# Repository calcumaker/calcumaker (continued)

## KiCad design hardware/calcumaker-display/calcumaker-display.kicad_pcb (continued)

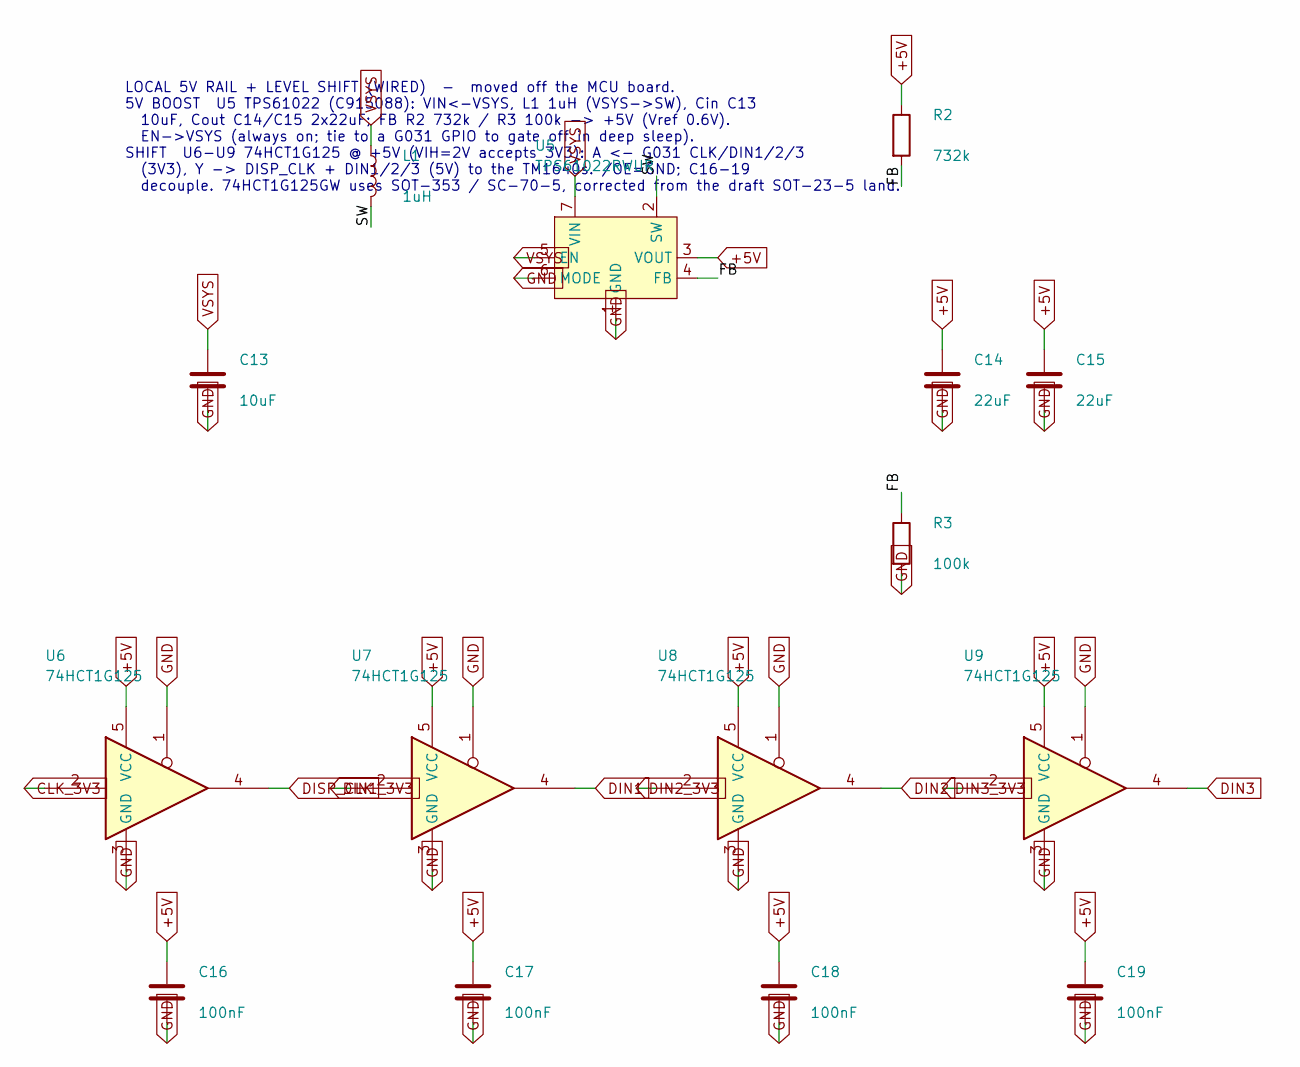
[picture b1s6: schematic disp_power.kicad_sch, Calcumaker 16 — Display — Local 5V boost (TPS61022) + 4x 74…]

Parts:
C13: 10uF; C_0603_1608Metric; LCSC C15850
C14, C15: 22uF; C_0603_1608Metric; LCSC C45783
C16, C17, C18, C19: 100nF; C_0402_1005Metric; LCSC C1525
L1: 1uH; L_0805_2012Metric; MPN FTC201610S1R0MBCA; LCSC C5832342
R2: 732k; R_0402_1005Metric
R3: 100k; R_0402_1005Metric; LCSC C25741
U5: TPS61022RWUR; Texas_RWU0007A_VQFN-7_2x2mm_P0.5mm; MPN TPS61022RWUR; LCSC C915088
U6, U7, U8, U9: 74HCT1G125; SOT-353_SC-70-5; MPN 74HCT1G125GW; LCSC C547448

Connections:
+5V: C14.1, C15.1, C16.1, C17.1, C18.1, C19.1, R2.1, U5.3 (VOUT), U6.5 (VCC), U7.5 (VCC), U8.5 (VCC), U9.5 (VCC); also elsewhere on the board
/DispPower/FB: R2.2, R3.1, U5.4 (FB)
/DispPower/SW: L1.2, U5.2 (SW)
CLK_3V3: U6.2; also elsewhere on the board
DIN1: U7.4; also elsewhere on the board
DIN1_3V3: U7.2; also elsewhere on the board
DIN2: U8.4; also elsewhere on the board
DIN2_3V3: U8.2; also elsewhere on the board
DIN3: U9.4; also elsewhere on the board
DIN3_3V3: U9.2; also elsewhere on the board
DISP_CLK: U6.4; also elsewhere on the board
GND: C13.2, C14.2, C15.2, C16.2, C17.2, C18.2, C19.2, R3.2, U5.1 (GND), U5.6 (MODE), U6.1, U6.3 (GND), U7.1, U7.3 (GND), U8.1, U8.3 (GND), U9.1, U9.3 (GND); also elsewhere on the board
VSYS: C13.1, L1.1, U5.5 (EN), U5.7 (VIN); also elsewhere on the board

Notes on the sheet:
LOCAL 5V RAIL + LEVEL SHIFT (WIRED) - moved off the MCU board. 5V BOOST U5 TPS61022 (C915088): VIN<-VSYS, L1 1uH (VSYS->SW), Cin C13 10uF, Cout C14/C15 2x22uF; FB R2 732k / R3 100k -> +5V (Vref 0.6V). EN->VSYS (always on; tie to a G031 GPIO to gate off in deep sleep). SHIFT U6-U9 74HCT1G125 @ +5V (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

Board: 2 copper layers, 86 parts (37 on the bottom side), 96 nets, no tracks yet.

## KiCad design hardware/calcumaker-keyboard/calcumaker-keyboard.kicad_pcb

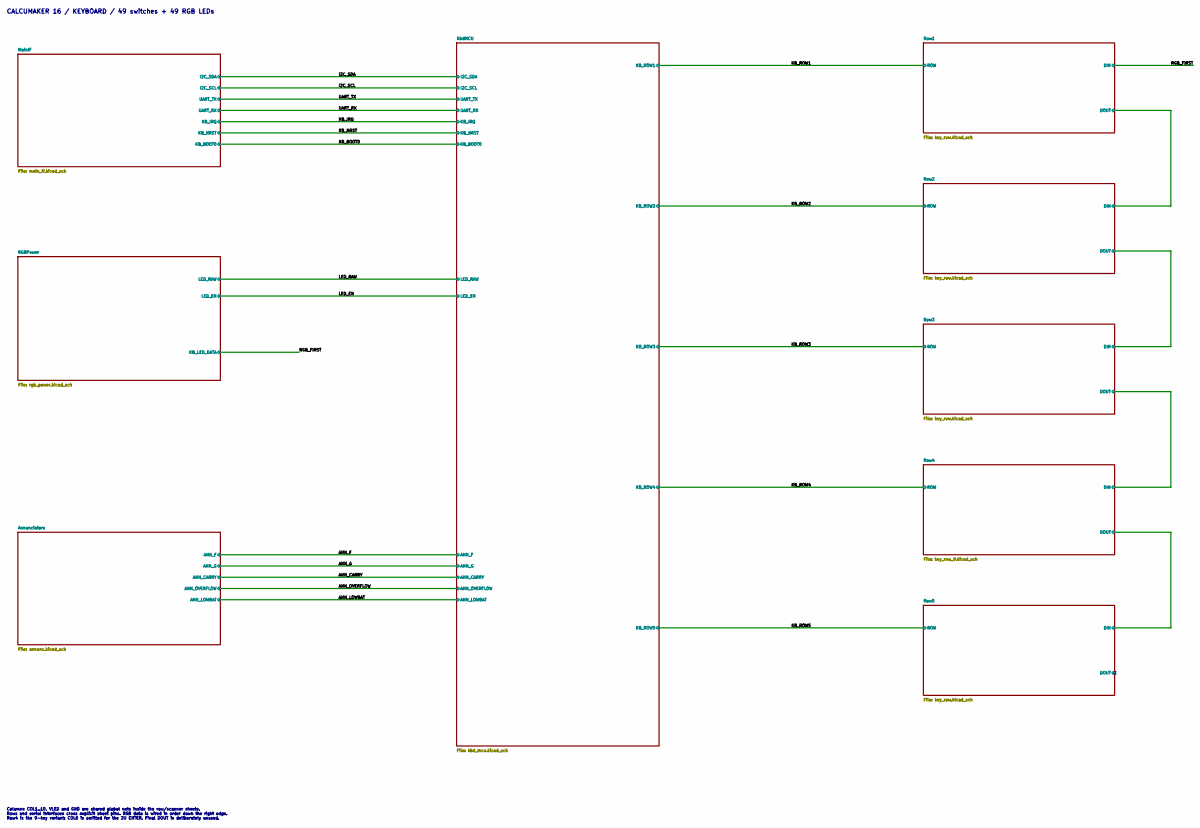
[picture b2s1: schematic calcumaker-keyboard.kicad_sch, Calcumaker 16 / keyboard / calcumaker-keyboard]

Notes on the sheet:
Columns COL1..10, VLED and GND are shared global nets inside the row/scanner sheets. Rows and serial interfaces cross explicit sheet pins. RGB data is wired in order down the right edge. Row4 is the 9-key variant: COL6 is omitted for the 2U ENTER. Final DOUT is deliberately unused.
CALCUMAKER 16 / KEYBOARD / 49 switches + 49 RGB LEDs

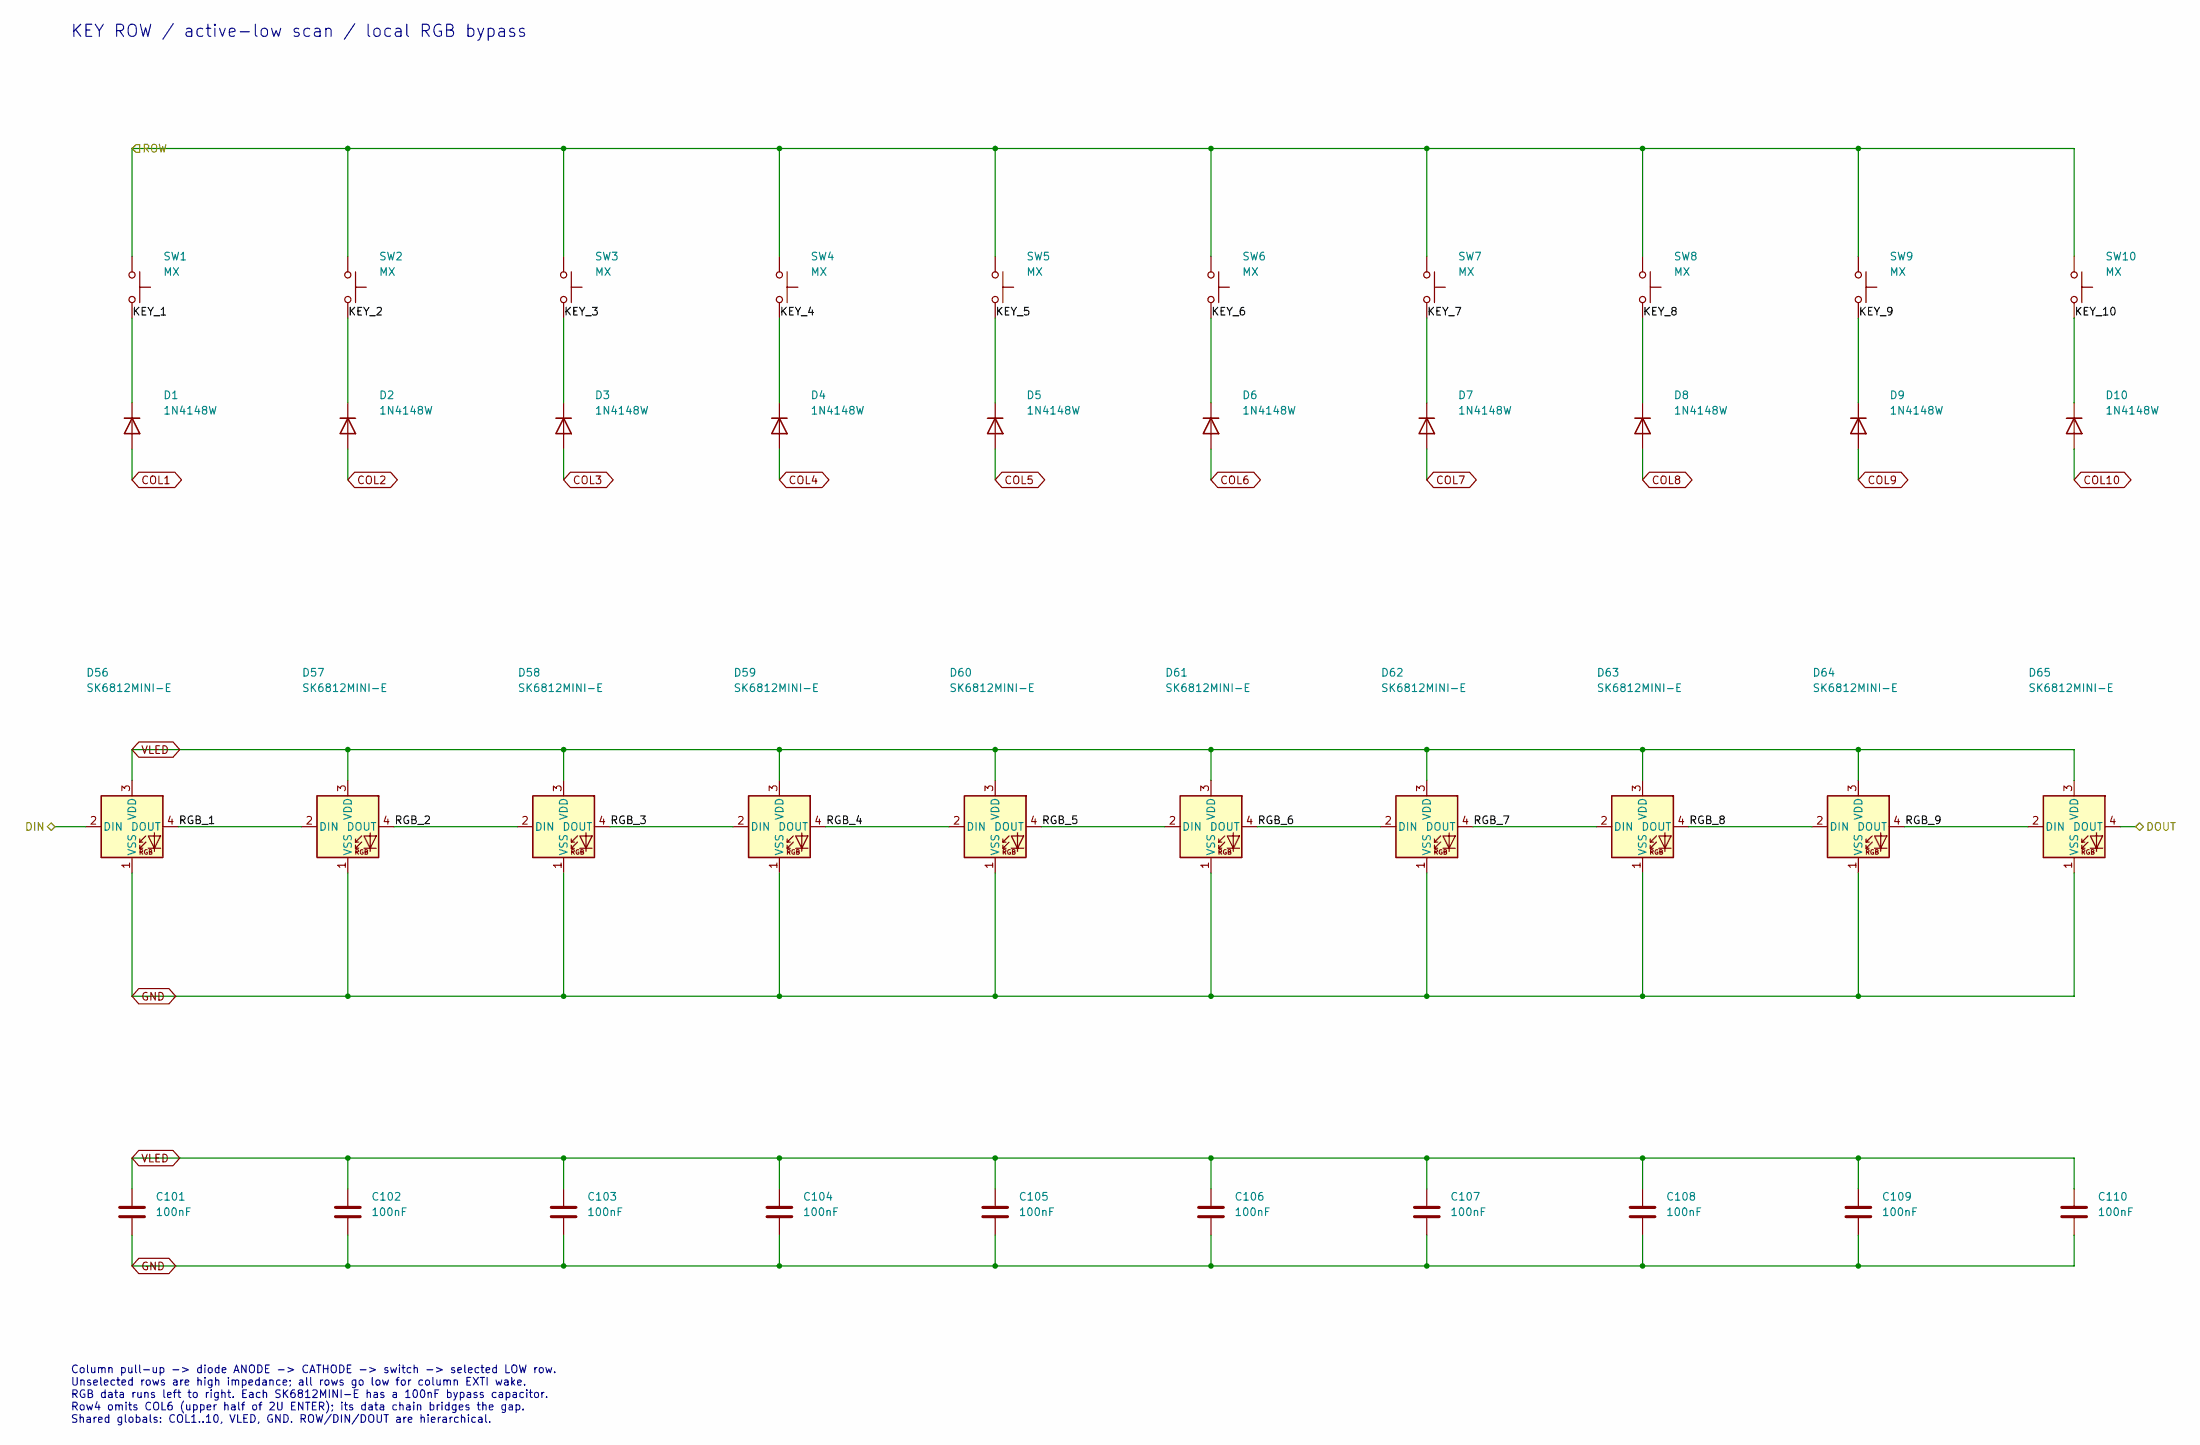
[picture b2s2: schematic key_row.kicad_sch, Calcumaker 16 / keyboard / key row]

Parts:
C101, C102, C103, C104, C105, C106, C107, C108, C109, C110: 100nF; C_0402_1005Metric
D1, D2, D3, D4, D5, D6, D7, D8, D9, D10: 1N4148W; D_SOD-123; MPN 1N4148W; LCSC C81598
D56, D57, D58, D59, D60, D61, D62, D63, D64, D65: SK6812MINI-E; LED_SK6812MINI-E_3.2x2.8mm_P1.5mm_ReverseMount; MPN SK6812MINI-E; LCSC C5149201
SW1, SW2, SW3, SW4, SW5, SW6, SW7, SW8, SW9, SW10: MX; SW_MX_HS_CPG151101S11_1u

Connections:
/KB_ROW1: SW1.1, SW2.1, SW3.1, SW4.1, SW5.1, SW6.1, SW7.1, SW8.1, SW9.1, SW10.1; also elsewhere on the board
/RGB_FIRST: D56.2 (DIN); also elsewhere on the board
/Row1/DOUT: D65.4 (DOUT); also elsewhere on the board
/Row1/KEY_1: D1.1 (K), SW1.2
/Row1/KEY_2: D2.1 (K), SW2.2
/Row1/KEY_3: D3.1 (K), SW3.2
/Row1/KEY_4: D4.1 (K), SW4.2
/Row1/KEY_5: D5.1 (K), SW5.2
/Row1/KEY_6: D6.1 (K), SW6.2
/Row1/KEY_7: D7.1 (K), SW7.2
/Row1/KEY_8: D8.1 (K), SW8.2
/Row1/KEY_9: D9.1 (K), SW9.2
/Row1/KEY_10: D10.1 (K), SW10.2
/Row1/RGB_1: D56.4 (DOUT), D57.2 (DIN)
/Row1/RGB_2: D57.4 (DOUT), D58.2 (DIN)
/Row1/RGB_3: D58.4 (DOUT), D59.2 (DIN)
/Row1/RGB_4: D59.4 (DOUT), D60.2 (DIN)
/Row1/RGB_5: D60.4 (DOUT), D61.2 (DIN)
/Row1/RGB_6: D61.4 (DOUT), D62.2 (DIN)
/Row1/RGB_7: D62.4 (DOUT), D63.2 (DIN)
/Row1/RGB_8: D63.4 (DOUT), D64.2 (DIN)
/Row1/RGB_9: D64.4 (DOUT), D65.2 (DIN)
COL1: D1.2 (A); also elsewhere on the board
COL2: D2.2 (A); also elsewhere on the board
COL3: D3.2 (A); also elsewhere on the board
COL4: D4.2 (A); also elsewhere on the board
COL5: D5.2 (A); also elsewhere on the board
COL6: D6.2 (A); also elsewhere on the board
COL7: D7.2 (A); also elsewhere on the board
COL8: D8.2 (A); also elsewhere on the board
COL9: D9.2 (A); also elsewhere on the board
COL10: D10.2 (A); also elsewhere on the board
GND: C101.2, C102.2, C103.2, C104.2, C105.2, C106.2, C107.2, C108.2, C109.2, C110.2, D56.1 (VSS), D57.1 (VSS), D58.1 (VSS), D59.1 (VSS), D60.1 (VSS), D61.1 (VSS), D62.1 (VSS), D63.1 (VSS), D64.1 (VSS), D65.1 (VSS); also elsewhere on the board
VLED: C101.1, C102.1, C103.1, C104.1, C105.1, C106.1, C107.1, C108.1, C109.1, C110.1, D56.3 (VDD), D57.3 (VDD), D58.3 (VDD), D59.3 (VDD), D60.3 (VDD), D61.3 (VDD), D62.3 (VDD), D63.3 (VDD), D64.3 (VDD), D65.3 (VDD); also elsewhere on the board

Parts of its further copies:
C111, C112, C113, C114, C115, C116, C117, C118, C119, C120, C121, C122, C123, C124, C125, C126, C127, C128, C129, C130, C141, C142, C143, C144, C145, C146, C147, C148, C149, C150: 100nF; C_0402_1005Metric
D11, D12, D13, D14, D15, D16, D17, D18, D19, D20, D21, D22, D23, D24, D25, D26, D27, D28, D29, D30, D41, D42, D43, D44, D45, D46, D47, D48, D49, D50: 1N4148W; D_SOD-123; MPN 1N4148W; LCSC C81598
D66, D67, D68, D69, D70, D71, D72, D73, D74, D75, D76, D77, D78, D79, D80, D81, D82, D83, D84, D85, D96, D97, D98, D99, D100, D101, D102, D103, D104, D105: SK6812MINI-E; LED_SK6812MINI-E_3.2x2.8mm_P1.5mm_ReverseMount; MPN SK6812MINI-E; LCSC C5149201
SW11, SW12, SW13, SW14, SW15, SW16, SW17, SW18, SW19, SW20, SW21, SW22, SW23, SW24, SW25, SW26, SW27, SW28, SW29, SW30, SW41, SW42, SW43, SW44, SW45, SW46, SW47, SW48, SW49, SW50: MX; SW_MX_HS_CPG151101S11_1u

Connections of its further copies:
/KB_ROW2: SW11.1, SW12.1, SW13.1, SW14.1, SW15.1, SW16.1, SW17.1, SW18.1, SW19.1, SW20.1; also elsewhere on the board
/KB_ROW3: SW21.1, SW22.1, SW23.1, SW24.1, SW25.1, SW26.1, SW27.1, SW28.1, SW29.1, SW30.1; also elsewhere on the board
/KB_ROW5: SW41.1, SW42.1, SW43.1, SW44.1, SW45.1, SW46.1, SW47.1, SW48.1, SW49.1, SW50.1; also elsewhere on the board
/Row1/DOUT: D66.2 (DIN); also elsewhere on the board
/Row2/DOUT: D75.4 (DOUT), D76.2 (DIN)
/Row2/KEY_1: D11.1 (K), SW11.2
/Row2/KEY_2: D12.1 (K), SW12.2
/Row2/KEY_3: D13.1 (K), SW13.2
/Row2/KEY_4: D14.1 (K), SW14.2
/Row2/KEY_5: D15.1 (K), SW15.2
/Row2/KEY_6: D16.1 (K), SW16.2
/Row2/KEY_7: D17.1 (K), SW17.2
/Row2/KEY_8: D18.1 (K), SW18.2
/Row2/KEY_9: D19.1 (K), SW19.2
/Row2/KEY_10: D20.1 (K), SW20.2
/Row2/RGB_1: D66.4 (DOUT), D67.2 (DIN)
/Row2/RGB_2: D67.4 (DOUT), D68.2 (DIN)
/Row2/RGB_3: D68.4 (DOUT), D69.2 (DIN)
/Row2/RGB_4: D69.4 (DOUT), D70.2 (DIN)
/Row2/RGB_5: D70.4 (DOUT), D71.2 (DIN)
/Row2/RGB_6: D71.4 (DOUT), D72.2 (DIN)
/Row2/RGB_7: D72.4 (DOUT), D73.2 (DIN)
/Row2/RGB_8: D73.4 (DOUT), D74.2 (DIN)
/Row2/RGB_9: D74.4 (DOUT), D75.2 (DIN)
/Row3/DOUT: D85.4 (DOUT); also elsewhere on the board
/Row3/KEY_1: D21.1 (K), SW21.2
/Row3/KEY_2: D22.1 (K), SW22.2
/Row3/KEY_3: D23.1 (K), SW23.2
/Row3/KEY_4: D24.1 (K), SW24.2
/Row3/KEY_5: D25.1 (K), SW25.2
/Row3/KEY_6: D26.1 (K), SW26.2
/Row3/KEY_7: D27.1 (K), SW27.2
/Row3/KEY_8: D28.1 (K), SW28.2
/Row3/KEY_9: D29.1 (K), SW29.2
/Row3/KEY_10: D30.1 (K), SW30.2
/Row3/RGB_1: D76.4 (DOUT), D77.2 (DIN)
/Row3/RGB_2: D77.4 (DOUT), D78.2 (DIN)
/Row3/RGB_3: D78.4 (DOUT), D79.2 (DIN)
/Row3/RGB_4: D79.4 (DOUT), D80.2 (DIN)
/Row3/RGB_5: D80.4 (DOUT), D81.2 (DIN)
/Row3/RGB_6: D81.4 (DOUT), D82.2 (DIN)
/Row3/RGB_7: D82.4 (DOUT), D83.2 (DIN)
/Row3/RGB_8: D83.4 (DOUT), D84.2 (DIN)
/Row3/RGB_9: D84.4 (DOUT), D85.2 (DIN)
/Row4/DOUT: D96.2 (DIN); also elsewhere on the board
/Row5/DOUT: D105.4 (DOUT)
/Row5/KEY_1: D41.1 (K), SW41.2
/Row5/KEY_2: D42.1 (K), SW42.2
/Row5/KEY_3: D43.1 (K), SW43.2
/Row5/KEY_4: D44.1 (K), SW44.2
/Row5/KEY_5: D45.1 (K), SW45.2
/Row5/KEY_6: D46.1 (K), SW46.2
/Row5/KEY_7: D47.1 (K), SW47.2
/Row5/KEY_8: D48.1 (K), SW48.2
/Row5/KEY_9: D49.1 (K), SW49.2
/Row5/KEY_10: D50.1 (K), SW50.2
/Row5/RGB_1: D96.4 (DOUT), D97.2 (DIN)
/Row5/RGB_2: D97.4 (DOUT), D98.2 (DIN)
/Row5/RGB_3: D98.4 (DOUT), D99.2 (DIN)
/Row5/RGB_4: D99.4 (DOUT), D100.2 (DIN)
/Row5/RGB_5: D100.4 (DOUT), D101.2 (DIN)
/Row5/RGB_6: D101.4 (DOUT), D102.2 (DIN)
/Row5/RGB_7: D102.4 (DOUT), D103.2 (DIN)
/Row5/RGB_8: D103.4 (DOUT), D104.2 (DIN)
/Row5/RGB_9: D104.4 (DOUT), D105.2 (DIN)
COL1: D11.2 (A), D21.2 (A), D41.2 (A); also elsewhere on the board
COL2: D12.2 (A), D22.2 (A), D42.2 (A); also elsewhere on the board
COL3: D13.2 (A), D23.2 (A), D43.2 (A); also elsewhere on the board
COL4: D14.2 (A), D24.2 (A), D44.2 (A); also elsewhere on the board
COL5: D15.2 (A), D25.2 (A), D45.2 (A); also elsewhere on the board
COL6: D16.2 (A), D26.2 (A), D46.2 (A); also elsewhere on the board
COL7: D17.2 (A), D27.2 (A), D47.2 (A); also elsewhere on the board
COL8: D18.2 (A), D28.2 (A), D48.2 (A); also elsewhere on the board
COL9: D19.2 (A), D29.2 (A), D49.2 (A); also elsewhere on the board
COL10: D20.2 (A), D30.2 (A), D50.2 (A); also elsewhere on the board
GND: C111.2, C112.2, C113.2, C114.2, C115.2, C116.2, C117.2, C118.2, C119.2, C120.2, C121.2, C122.2, C123.2, C124.2, C125.2, C126.2, C127.2, C128.2, C129.2, C130.2, C141.2, C142.2, C143.2, C144.2, C145.2, C146.2, C147.2, C148.2, C149.2, C150.2, D66.1 (VSS), D67.1 (VSS), D68.1 (VSS), D69.1 (VSS), D70.1 (VSS), D71.1 (VSS), D72.1 (VSS), D73.1 (VSS), D74.1 (VSS), D75.1 (VSS), D76.1 (VSS), D77.1 (VSS), D78.1 (VSS), D79.1 (VSS), D80.1 (VSS), D81.1 (VSS), D82.1 (VSS), D83.1 (VSS), D84.1 (VSS), D85.1 (VSS), D96.1 (VSS), D97.1 (VSS), D98.1 (VSS), D99.1 (VSS), D100.1 (VSS), D101.1 (VSS), D102.1 (VSS), D103.1 (VSS), D104.1 (VSS), D105.1 (VSS); also elsewhere on the board
VLED: C111.1, C112.1, C113.1, C114.1, C115.1, C116.1, C117.1, C118.1, C119.1, C120.1, C121.1, C122.1, C123.1, C124.1, C125.1, C126.1, C127.1, C128.1, C129.1, C130.1, C141.1, C142.1, C143.1, C144.1, C145.1, C146.1, C147.1, C148.1, C149.1, C150.1, D66.3 (VDD), D67.3 (VDD), D68.3 (VDD), D69.3 (VDD), D70.3 (VDD), D71.3 (VDD), D72.3 (VDD), D73.3 (VDD), D74.3 (VDD), D75.3 (VDD), D76.3 (VDD), D77.3 (VDD), D78.3 (VDD), D79.3 (VDD), D80.3 (VDD), D81.3 (VDD), D82.3 (VDD), D83.3 (VDD), D84.3 (VDD), D85.3 (VDD), D96.3 (VDD), D97.3 (VDD), D98.3 (VDD), D99.3 (VDD), D100.3 (VDD), D101.3 (VDD), D102.3 (VDD), D103.3 (VDD), D104.3 (VDD), D105.3 (VDD); also elsewhere on the board

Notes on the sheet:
KEY ROW / active-low scan / local RGB bypass
Column pull-up -> diode ANODE -> CATHODE -> switch -> selected LOW row. Unselected rows are high impedance; all rows go low for column EXTI wake. RGB data runs left to right. Each SK6812MINI-E has a 100nF bypass capacitor. Row4 omits COL6 (upper half of 2U ENTER); its data chain bridges the gap. Sh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

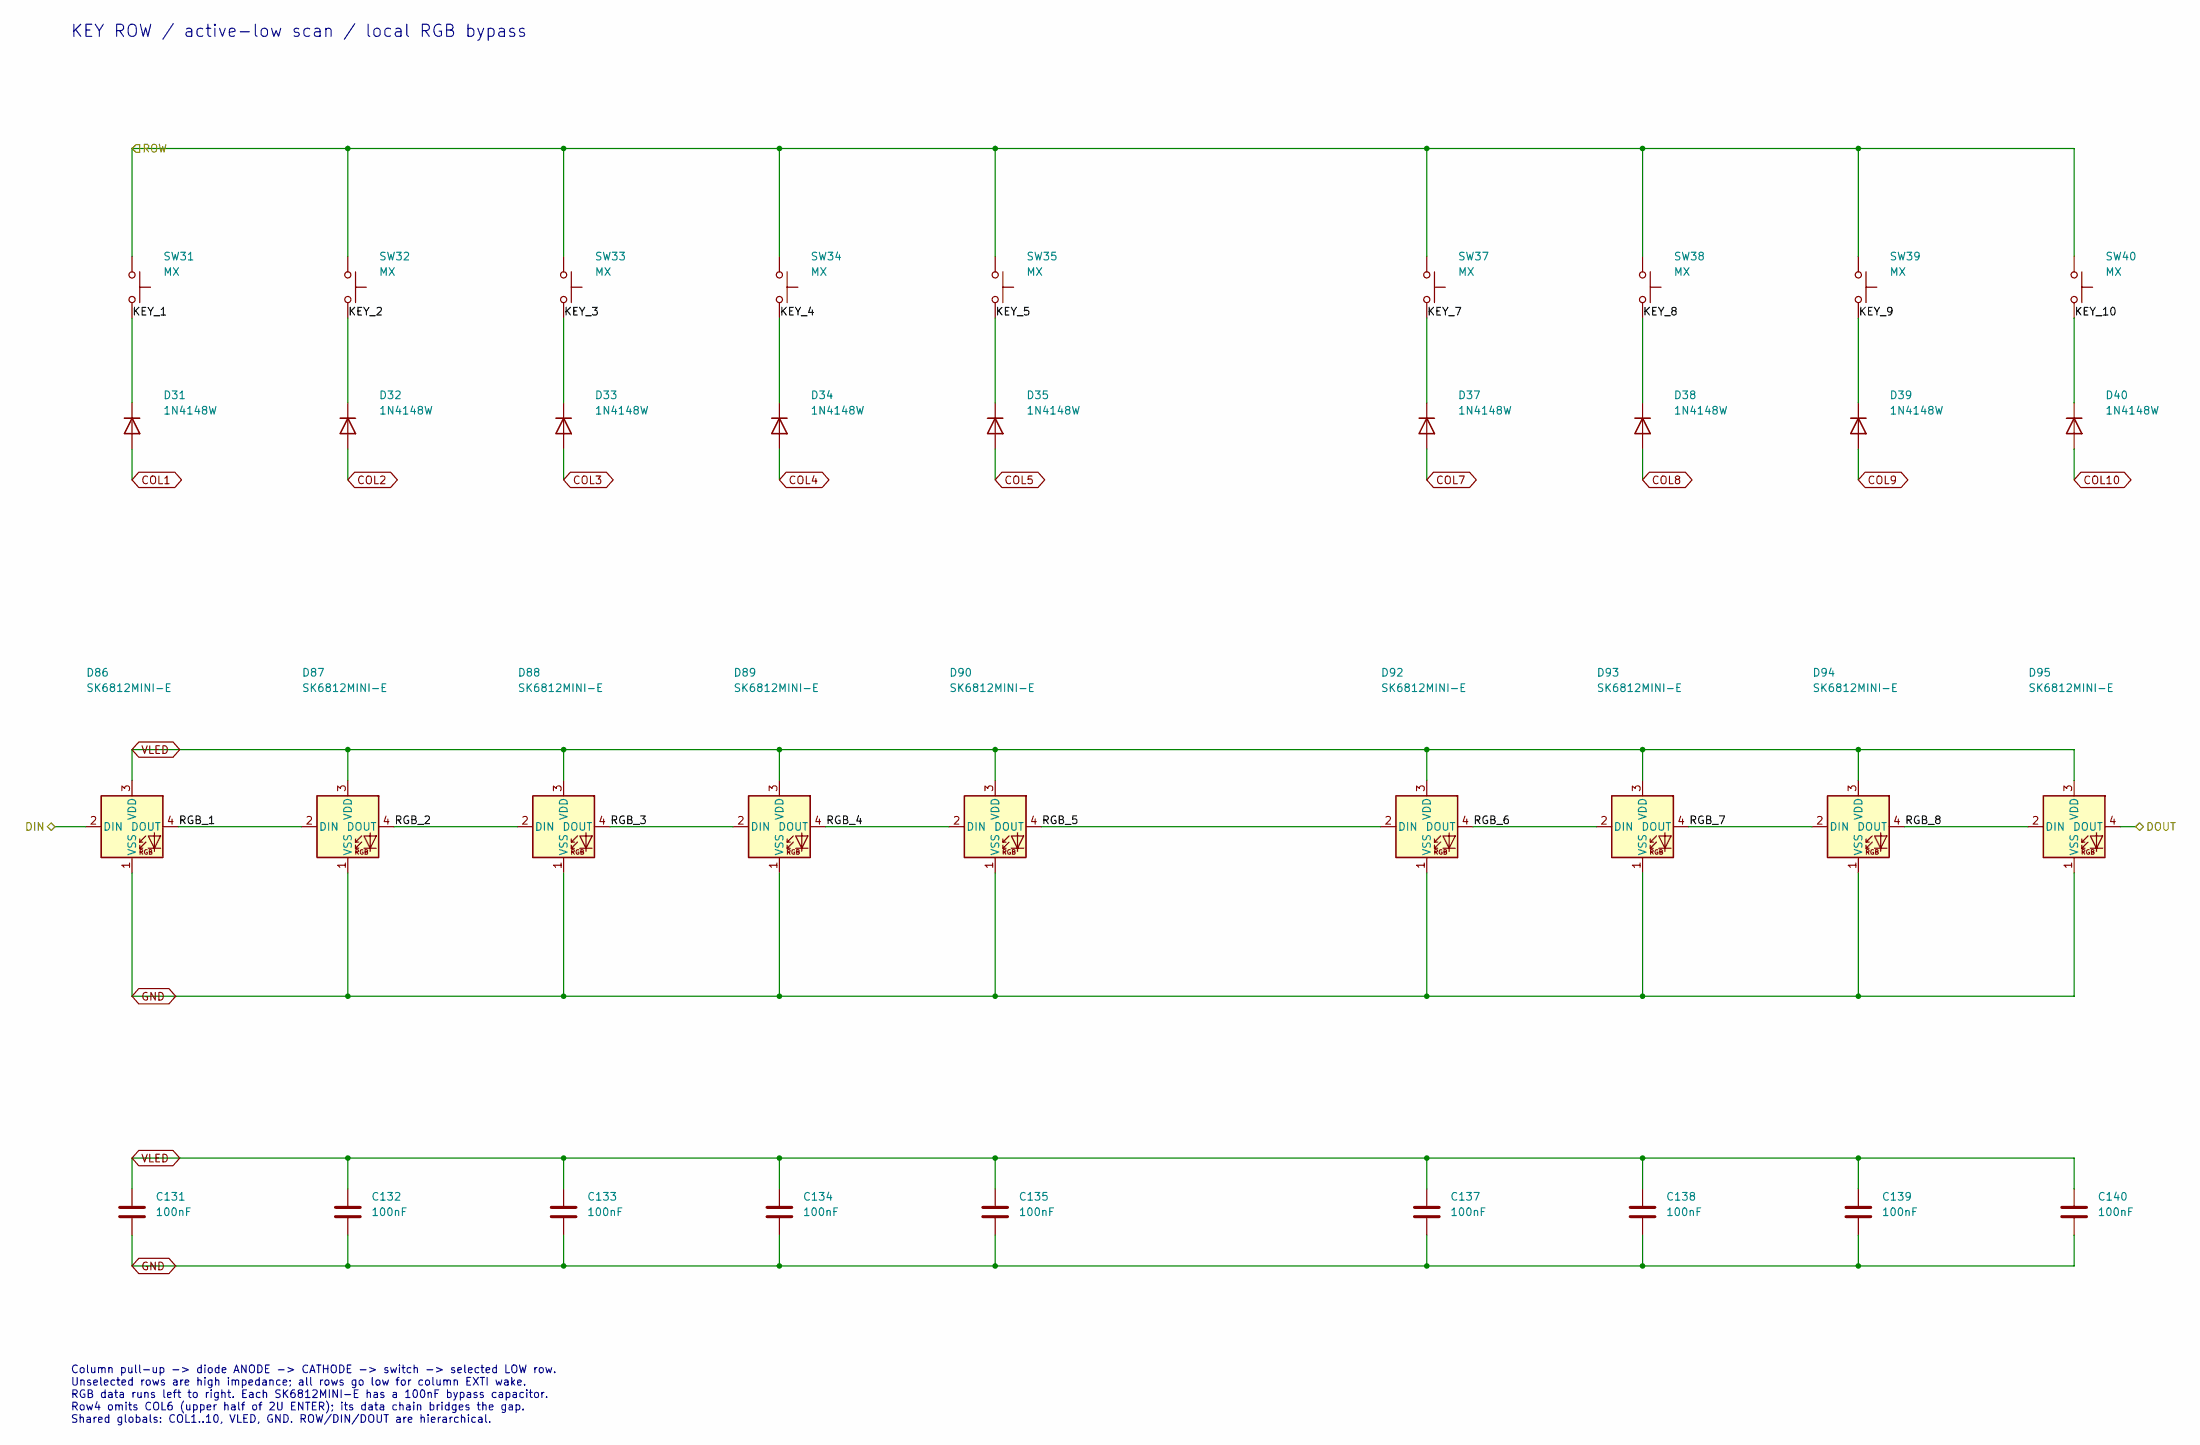
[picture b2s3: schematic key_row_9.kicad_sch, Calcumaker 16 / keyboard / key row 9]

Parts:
C131, C132, C133, C134, C135, C137, C138, C139, C140: 100nF; C_0402_1005Metric
D31, D32, D33, D34, D35, D37, D38, D39, D40: 1N4148W; D_SOD-123; MPN 1N4148W; LCSC C81598
D86, D87, D88, D89, D90, D92, D93, D94, D95: SK6812MINI-E; LED_SK6812MINI-E_3.2x2.8mm_P1.5mm_ReverseMount; MPN SK6812MINI-E; LCSC C5149201
SW31, SW32, SW33, SW34, SW35, SW37, SW38, SW39, SW40: MX; SW_MX_HS_CPG151101S11_1u

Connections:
/KB_ROW4: SW31.1, SW32.1, SW33.1, SW34.1, SW35.1, SW37.1, SW38.1, SW39.1, SW40.1; also elsewhere on the board
/Row3/DOUT: D86.2 (DIN); also elsewhere on the board
/Row4/DOUT: D95.4 (DOUT); also elsewhere on the board
/Row4/KEY_1: D31.1 (K), SW31.2
/Row4/KEY_2: D32.1 (K), SW32.2
/Row4/KEY_3: D33.1 (K), SW33.2
/Row4/KEY_4: D34.1 (K), SW34.2
/Row4/KEY_5: D35.1 (K), SW35.2
/Row4/KEY_7: D37.1 (K), SW37.2
/Row4/KEY_8: D38.1 (K), SW38.2
/Row4/KEY_9: D39.1 (K), SW39.2
/Row4/KEY_10: D40.1 (K), SW40.2
/Row4/RGB_1: D86.4 (DOUT), D87.2 (DIN)
/Row4/RGB_2: D87.4 (DOUT), D88.2 (DIN)
/Row4/RGB_3: D88.4 (DOUT), D89.2 (DIN)
/Row4/RGB_4: D89.4 (DOUT), D90.2 (DIN)
/Row4/RGB_5: D90.4 (DOUT), D92.2 (DIN)
/Row4/RGB_6: D92.4 (DOUT), D93.2 (DIN)
/Row4/RGB_7: D93.4 (DOUT), D94.2 (DIN)
/Row4/RGB_8: D94.4 (DOUT), D95.2 (DIN)
COL1: D31.2 (A); also elsewhere on the board
COL2: D32.2 (A); also elsewhere on the board
COL3: D33.2 (A); also elsewhere on the board
COL4: D34.2 (A); also elsewhere on the board
COL5: D35.2 (A); also elsewhere on the board
COL7: D37.2 (A); also elsewhere on the board
COL8: D38.2 (A); also elsewhere on the board
COL9: D39.2 (A); also elsewhere on the board
COL10: D40.2 (A); also elsewhere on the board
GND: C131.2, C132.2, C133.2, C134.2, C135.2, C137.2, C138.2, C139.2, C140.2, D86.1 (VSS), D87.1 (VSS), D88.1 (VSS), D89.1 (VSS), D90.1 (VSS), D92.1 (VSS), D93.1 (VSS), D94.1 (VSS), D95.1 (VSS); also elsewhere on the board
VLED: C131.1, C132.1, C133.1, C134.1, C135.1, C137.1, C138.1, C139.1, C140.1, D86.3 (VDD), D87.3 (VDD), D88.3 (VDD), D89.3 (VDD), D90.3 (VDD), D92.3 (VDD), D93.3 (VDD), D94.3 (VDD), D95.3 (VDD); also elsewhere on the board

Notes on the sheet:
Column pull-up -> diode ANODE -> CATHODE -> switch -> selected LOW row. Unselected rows are high impedance; all rows go low for column EXTI wake. RGB data runs left to right. Each SK6812MINI-E has a 100nF bypass capacitor. Row4 omits COL6 (upper half of 2U ENTER); its data chain bridges the gap. Sh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
KEY ROW / active-low scan / local RGB bypass

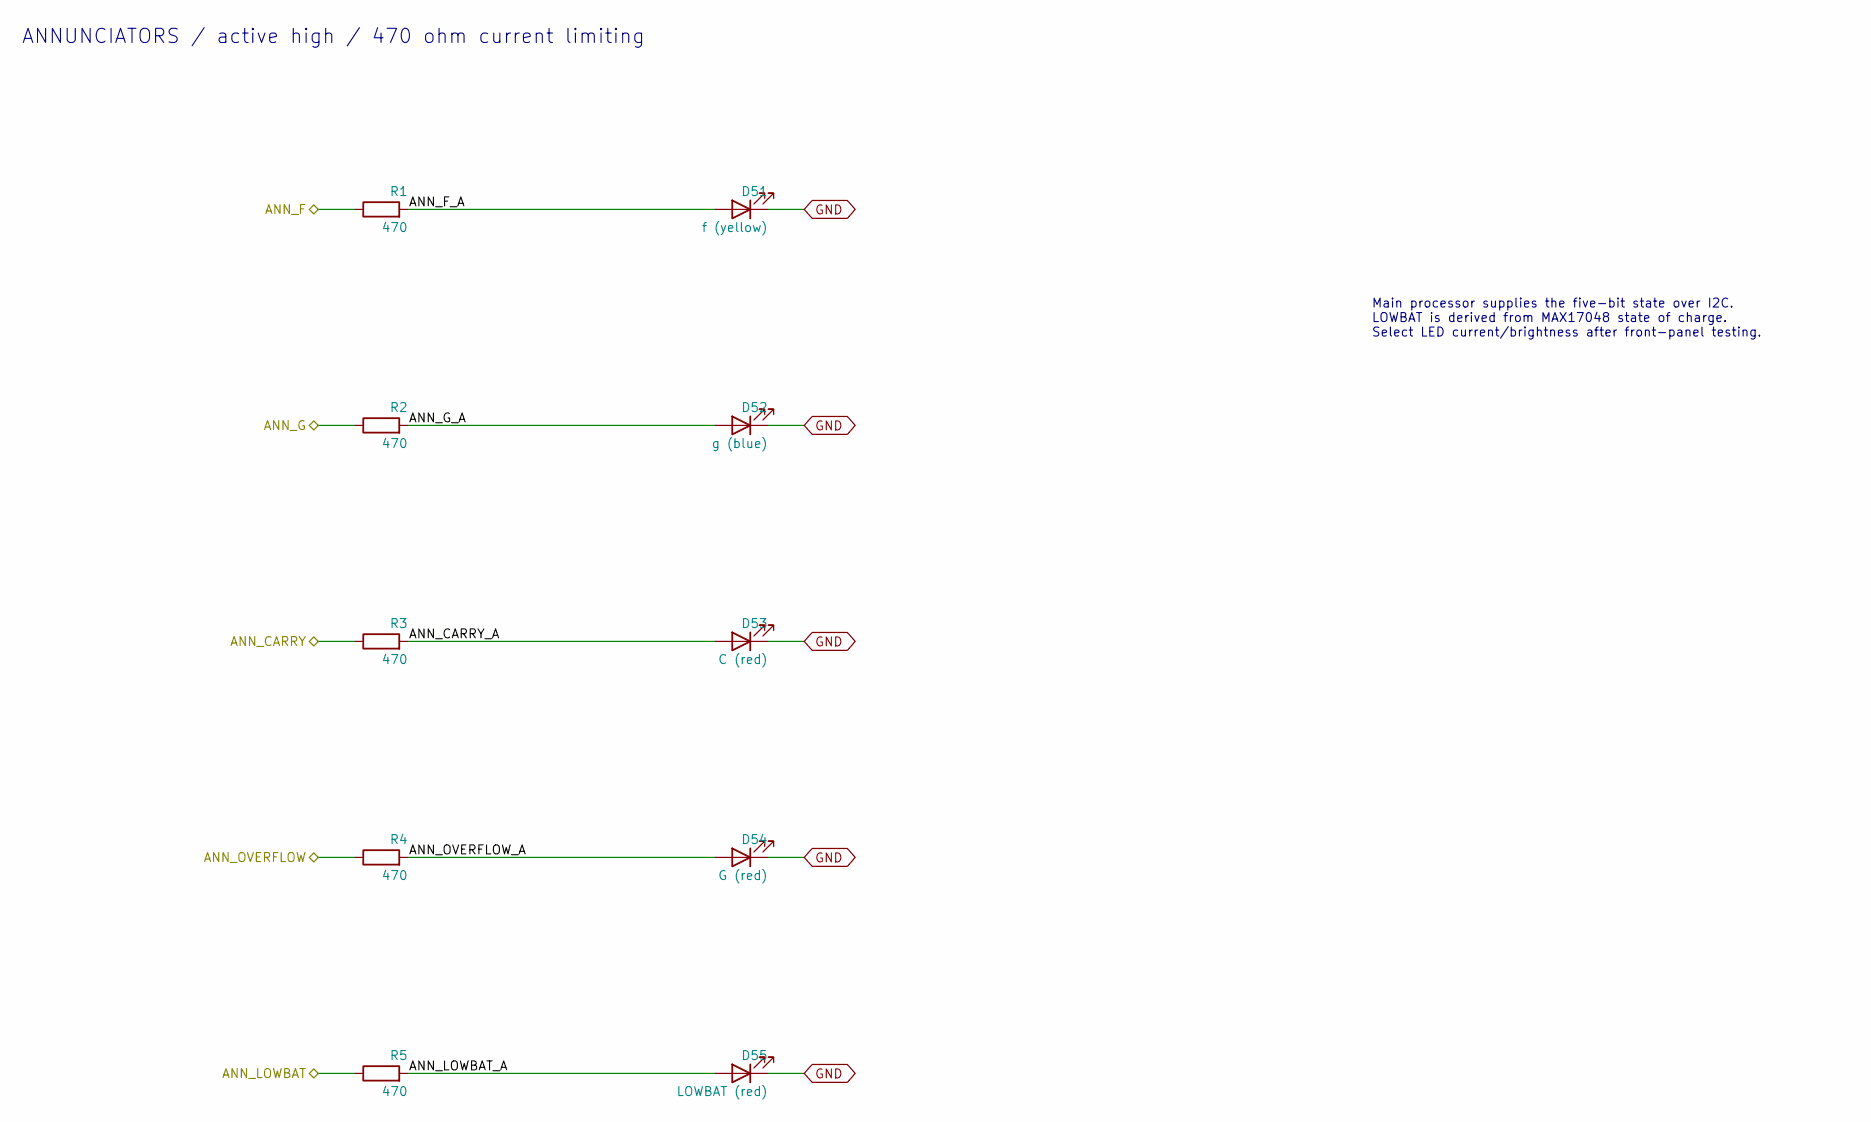
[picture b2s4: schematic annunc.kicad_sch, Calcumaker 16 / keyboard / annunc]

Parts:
D51: f (yellow); LED_0603_1608Metric; MPN 19-213/Y2C-CQ2R2L/3T(CY); LCSC C72038
D52: g (blue); LED_0603_1608Metric; MPN XL-1608UBC-04; LCSC C965807
D53: C (red); LED_0603_1608Metric; MPN KT-0603R; LCSC C2286
D54: G (red); LED_0603_1608Metric; MPN KT-0603R; LCSC C2286
D55: LOWBAT (red); LED_0603_1608Metric; MPN KT-0603R; LCSC C2286
R1, R2, R3, R4, R5: 470; R_0402_1005Metric; LCSC C25117

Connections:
/ANN_CARRY: R3.1; also elsewhere on the board
/ANN_F: R1.1; also elsewhere on the board
/ANN_G: R2.1; also elsewhere on the board
/ANN_LOWBAT: R5.1; also elsewhere on the board
/ANN_OVERFLOW: R4.1; also elsewhere on the board
/Annunciators/ANN_CARRY_A: D53.2 (A), R3.2
/Annunciators/ANN_F_A: D51.2 (A), R1.2
/Annunciators/ANN_G_A: D52.2 (A), R2.2
/Annunciators/ANN_LOWBAT_A: D55.2 (A), R5.2
/Annunciators/ANN_OVERFLOW_A: D54.2 (A), R4.2
GND: D51.1 (K), D52.1 (K), D53.1 (K), D54.1 (K), D55.1 (K); also elsewhere on the board

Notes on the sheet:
Main processor supplies the five-bit state over I2C. LOWBAT is derived from MAX17048 state of charge. Select LED current/brightness after front-panel testing.
ANNUNCIATORS / active high / 470 ohm current limiting
